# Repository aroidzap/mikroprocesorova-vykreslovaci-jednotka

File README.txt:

Copyright (c) 2015 Tomá Pazdiora

Documents, images, code, schematics and boards.

Documents, images, all schematic (.sch) and board (.brd) files are licenced under CC-BY 4.0 (http://creativecommons.org/licenses/by/4.0/legalcode)
All source code is licensed under MIT license. See the file "LICENSE.txt" for full license text.

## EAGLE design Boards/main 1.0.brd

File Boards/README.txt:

You can view and export boards using CadSoft's EAGLE Light Edition. (available from: http://www.cadsoftusa.com/download-eagle/freeware/)

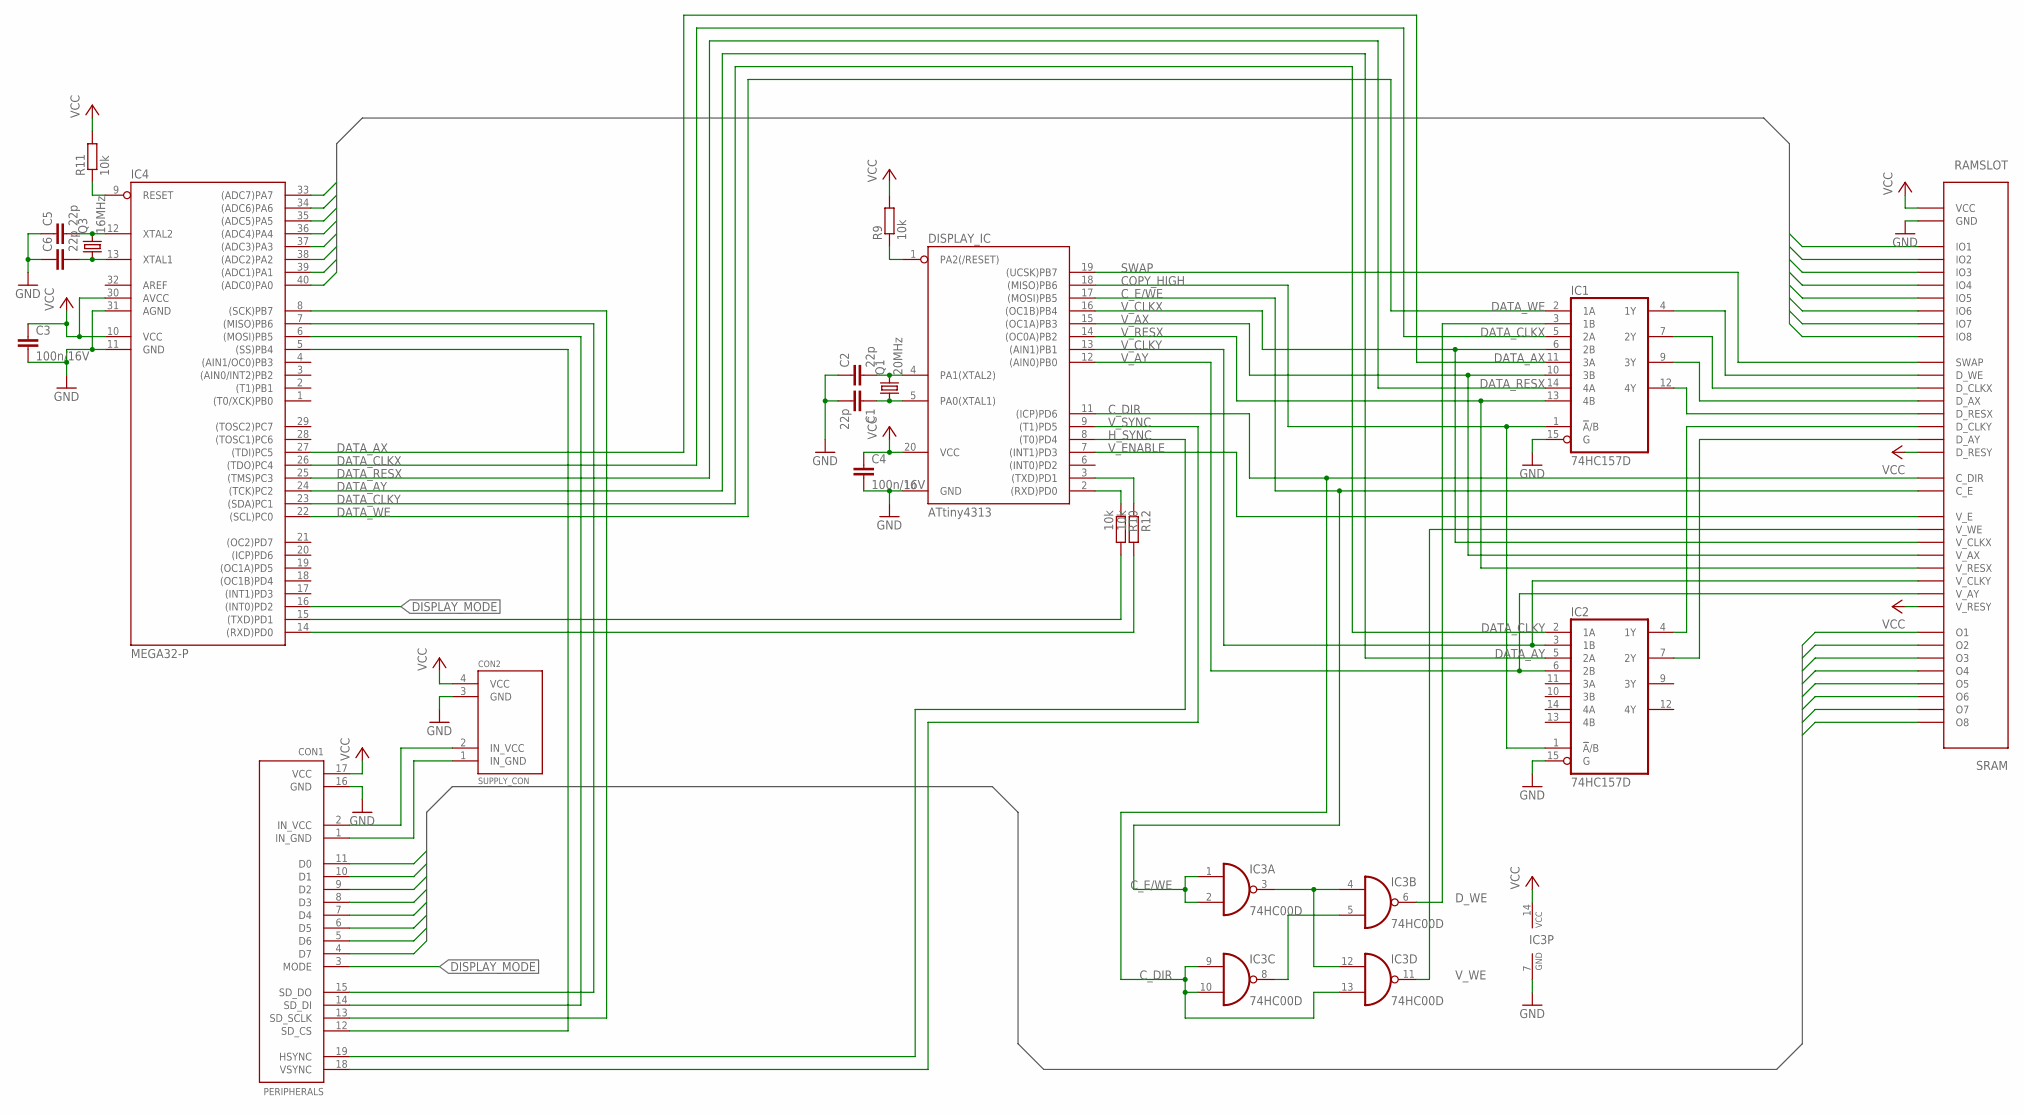
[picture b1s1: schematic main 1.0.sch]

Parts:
C1, C2, C5, C6: 22p; C0603
C3, C4: 100n/16V; C0603
CON1: PERIPHERALS; PERIPHERALS_CON
CON2: SUPPLY_CON
DISPLAY_IC: ATtiny4313; DIL20
IC1, IC2: 74HC157D; SO16
IC3: 74HC00D; SO14
IC4: MEGA32-P; DIL40
Q1: 20MHz; HC49
Q3: 16MHz; HC49
R9, R10, R11, R12: 10k; R0603
RAMSLOT: SRAM; SLOT

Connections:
AREF: IC4.32 (AREF)
COPY_HIGH: DISPLAY_IC.18 ((MISO)PB6), IC1.1 (!A!/B), IC2.1 (!A!/B)
C_DIR: DISPLAY_IC.11 ((ICP)PD6), IC3.9 (I0), IC3.10 (I1), IC3.13 (I1), RAMSLOT.C_DIR, RAMSLOT.C_DIRB (C_DIR)
C_E/WE: DISPLAY_IC.17 ((MOSI)PB5), IC3.1 (I0), IC3.2 (I1), RAMSLOT.C_E, RAMSLOT.C_EB (C_E)
DATA0: IC4.40 ((ADC0)PA0), RAMSLOT.IO1, RAMSLOT.IO1B (IO1)
DATA1: IC4.39 ((ADC1)PA1), RAMSLOT.IO2, RAMSLOT.IO2B (IO2)
DATA2: IC4.38 ((ADC2)PA2), RAMSLOT.IO3, RAMSLOT.IO3B (IO3)
DATA3: IC4.37 ((ADC3)PA3), RAMSLOT.IO4, RAMSLOT.IO4B (IO4)
DATA4: IC4.36 ((ADC4)PA4), RAMSLOT.IO5, RAMSLOT.IO5B (IO5)
DATA5: IC4.35 ((ADC5)PA5), RAMSLOT.IO6, RAMSLOT.IO6B (IO6)
DATA6: IC4.34 ((ADC6)PA6), RAMSLOT.IO7, RAMSLOT.IO7B (IO7)
DATA7: IC4.33 ((ADC7)PA7), RAMSLOT.IO8, RAMSLOT.IO8B (IO8)
DATA_AX: IC1.11 (3A), IC4.27 ((TDI)PC5)
DATA_AY: IC2.5 (2A), IC4.24 ((TCK)PC2)
DATA_CLKX: IC1.5 (2A), IC4.26 ((TDO)PC4)
DATA_CLKY: IC2.2 (1A), IC4.23 ((SDA)PC1)
DATA_RESX: IC1.14 (4A), IC4.25 ((TMS)PC3)
DATA_WE: IC1.2 (1A), IC4.22 ((SCL)PC0)
DISPLAY_MODE: CON1.3 (MODE), IC4.16 ((INT0)PD2)
D_WE: IC1.3 (1B), IC3.6 (O)
GND: C1.2, C2.1, C3.2, C4.2, C5.1, C6.1, CON1.16 (GND), CON2.3 (GND), DISPLAY_IC.10 (GND), IC1.8 (GND), IC1.15 (G), IC2.8 (GND), IC2.15 (G), IC3.7 (GND), IC4.11 (GND), IC4.31 (AGND), RAMSLOT.GND, RAMSLOT.GNDB (GND)
H_SYNC: CON1.19 (HSYNC), DISPLAY_IC.8 ((T0)PD4)
IN_GND: CON1.1 (IN_GND), CON2.1 (IN_GND)
MAIN_RX: IC4.14 ((RXD)PD0), R12.2
MAIN_TX: IC4.15 ((TXD)PD1), R10.2
unnamed: IC4.9 (RESET), R11.1
unnamed: IC3.3 (O), IC3.4 (I0), IC3.12 (I0)
unnamed: IC3.5 (I1), IC3.8 (O)
unnamed: CON1.2 (IN_VCC), CON2.2 (IN_VCC)
unnamed: DISPLAY_IC.1 (PA2(/RESET)), R9.1
unnamed: DISPLAY_IC.3 ((TXD)PD1), R12.1
unnamed: C5.2, IC4.12 (XTAL2), Q3.2
unnamed: C6.2, IC4.13 (XTAL1), Q3.1
unnamed: DISPLAY_IC.2 ((RXD)PD0), R10.1
unnamed: C1.1, DISPLAY_IC.5 (PA0(XTAL1)), Q1.1
unnamed: C2.2, DISPLAY_IC.4 (PA1(XTAL2)), Q1.2
unnamed: IC1.4 (1Y), RAMSLOT.D_WE, RAMSLOT.D_WEB (D_WE)
unnamed: IC1.7 (2Y), RAMSLOT.D_CLKX, RAMSLOT.D_CLKXB (D_CLKX)
unnamed: IC1.9 (3Y), RAMSLOT.D_AX, RAMSLOT.D_AXB (D_AX)
unnamed: IC1.12 (4Y), RAMSLOT.D_RESX, RAMSLOT.D_RESXB (D_RESX)
unnamed: IC2.4 (1Y), RAMSLOT.D_CLKY, RAMSLOT.D_CLKYB (D_CLKY)
unnamed: IC2.7 (2Y), RAMSLOT.D_AY, RAMSLOT.D_AYB (D_AY)
O0: CON1.11 (D0), RAMSLOT.O1, RAMSLOT.O1B (O1)
O1: CON1.10 (D1), RAMSLOT.O2, RAMSLOT.O2B (O2)
O2: CON1.9 (D2), RAMSLOT.O3, RAMSLOT.O3B (O3)
O3: CON1.8 (D3), RAMSLOT.O4, RAMSLOT.O4B (O4)
O4: CON1.7 (D4), RAMSLOT.O5, RAMSLOT.O5B (O5)
O5: CON1.6 (D5), RAMSLOT.O6, RAMSLOT.O6B (O6)
O6: CON1.5 (D6), RAMSLOT.O7, RAMSLOT.O7B (O7)
O7: CON1.4 (D7), RAMSLOT.O8, RAMSLOT.O8B (O8)
SD_CS: CON1.12 (SD_CS), IC4.5 ((SS)PB4)
SD_DI: CON1.14 (SD_DI), IC4.6 ((MOSI)PB5)
SD_DO: CON1.15 (SD_DO), IC4.7 ((MISO)PB6)
SD_SCLK: CON1.13 (SD_SCLK), IC4.8 ((SCK)PB7)
SWAP: DISPLAY_IC.19 ((UCSK)PB7), RAMSLOT.SWAP, RAMSLOT.SWAPB (SWAP)
VCC: C3.1, C4.1, CON1.17 (VCC), CON2.4 (VCC), DISPLAY_IC.20 (VCC), IC1.16 (VCC), IC2.16 (VCC), IC3.14 (VCC), IC4.10 (VCC), IC4.30 (AVCC), R9.2, R11.2, RAMSLOT.D_RESY, RAMSLOT.D_RESYB (D_RESY), RAMSLOT.VCC, RAMSLOT.VCCB (VCC), RAMSLOT.V_RESY, RAMSLOT.V_RESYB (V_RESY)
V_AX: DISPLAY_IC.15 ((OC1A)PB3), IC1.10 (3B), RAMSLOT.V_AX, RAMSLOT.V_AXB (V_AX)
V_AY: DISPLAY_IC.12 ((AIN0)PB0), IC2.6 (2B), RAMSLOT.V_AY, RAMSLOT.V_AYB (V_AY)
V_CLKX: DISPLAY_IC.16 ((OC1B)PB4), IC1.6 (2B), RAMSLOT.V_CLKX, RAMSLOT.V_CLKXB (V_CLKX)
V_CLKY: DISPLAY_IC.13 ((AIN1)PB1), IC2.3 (1B), RAMSLOT.V_CLKY, RAMSLOT.V_CLKYB (V_CLKY)
V_ENABLE: DISPLAY_IC.7 ((INT1)PD3), RAMSLOT.V_E, RAMSLOT.V_EB (V_E)
V_RESX: DISPLAY_IC.14 ((OC0A)PB2), IC1.13 (4B), RAMSLOT.V_RESX, RAMSLOT.V_RESXB (V_RESX)
V_SYNC: CON1.18 (VSYNC), DISPLAY_IC.9 ((T1)PD5)
V_WE: IC3.11 (O), RAMSLOT.V_WE, RAMSLOT.V_WEB (V_WE)

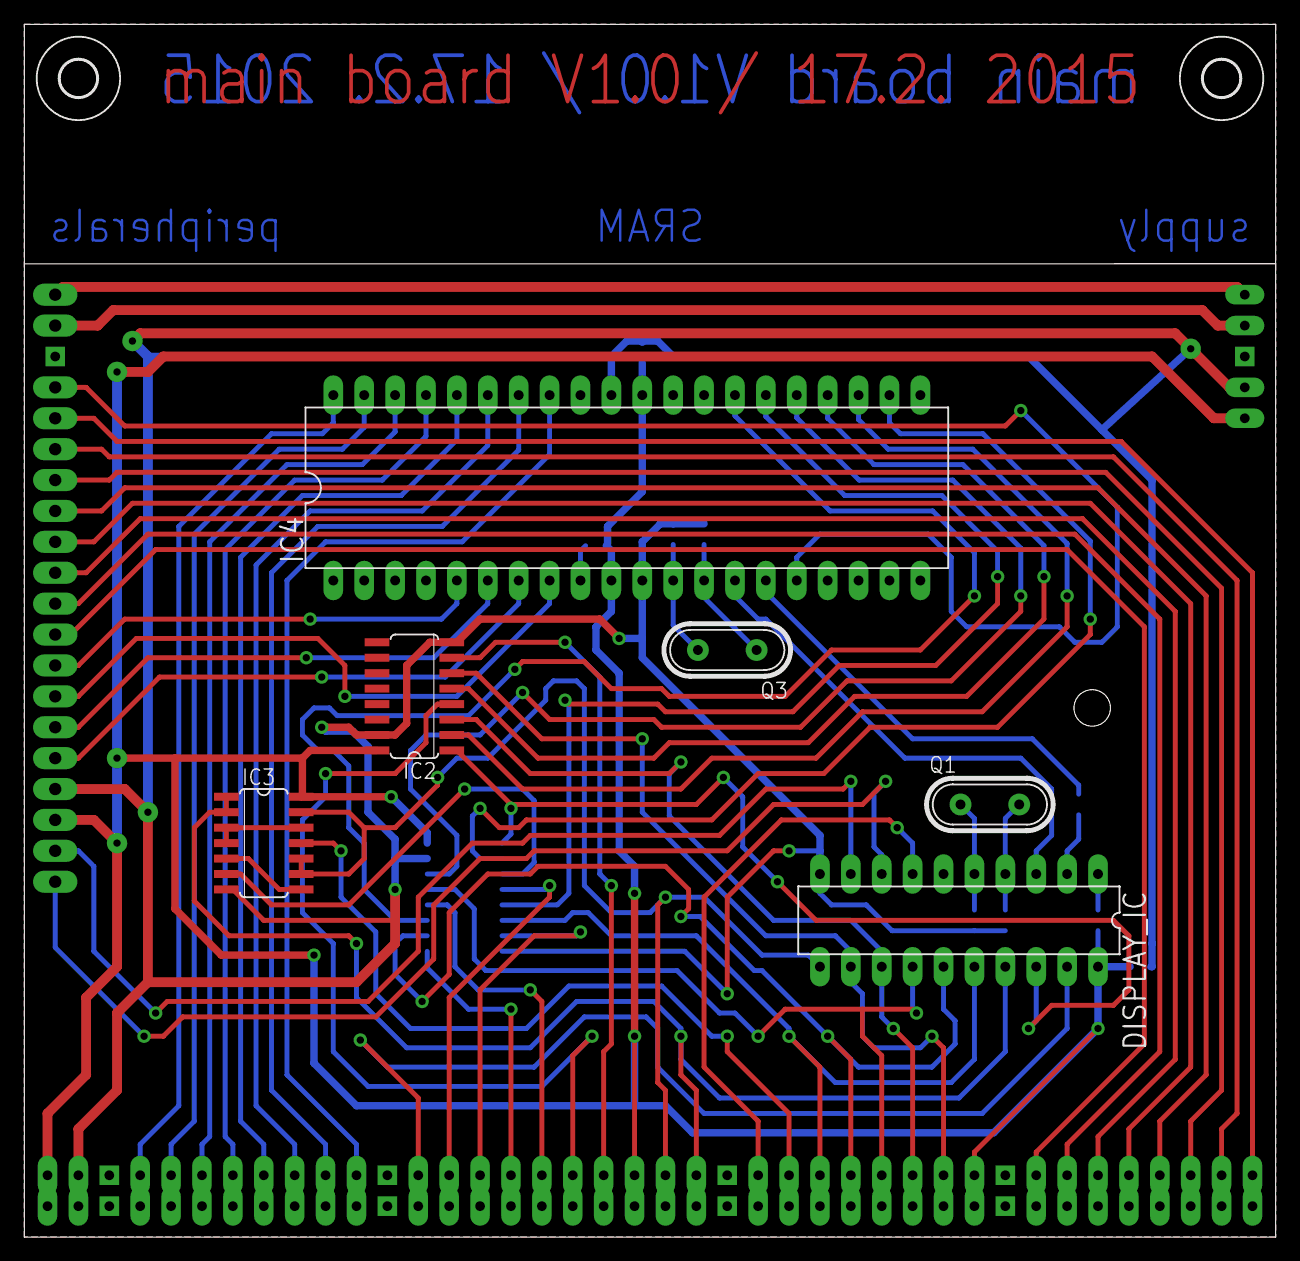
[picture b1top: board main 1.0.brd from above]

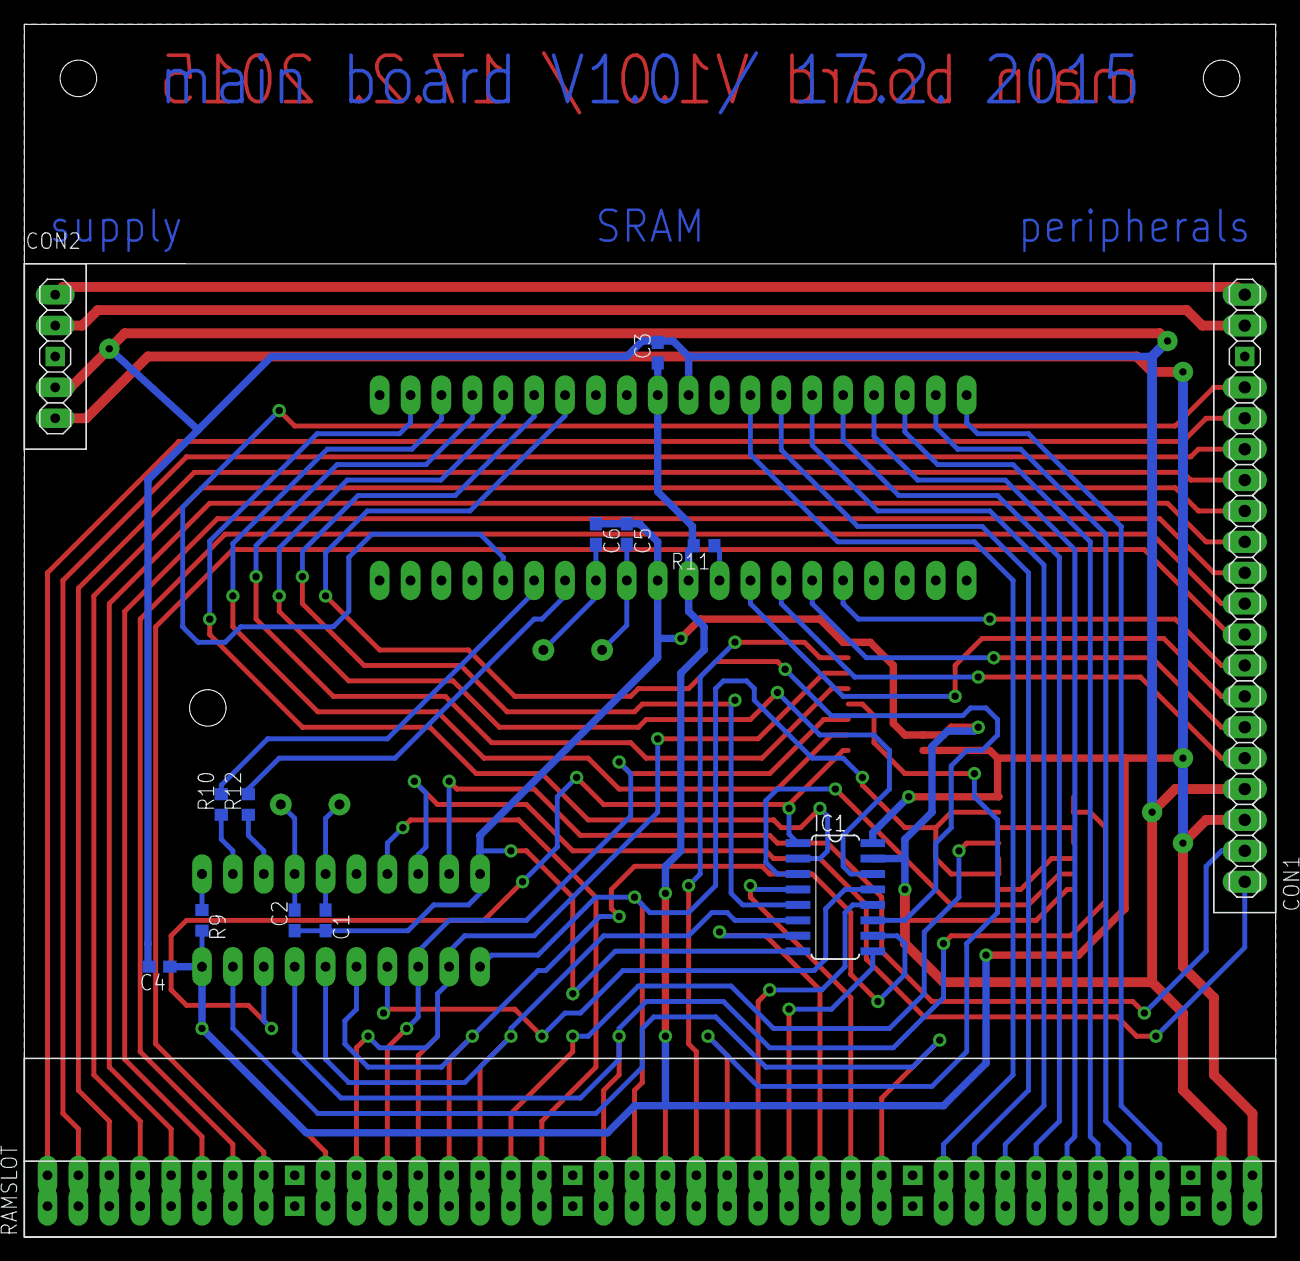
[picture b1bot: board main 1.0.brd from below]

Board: 2 copper layers, 102.9 x 99.7 mm, 22 parts (14 on the bottom side), 63 nets.

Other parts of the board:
U$1, U$2: 3,0

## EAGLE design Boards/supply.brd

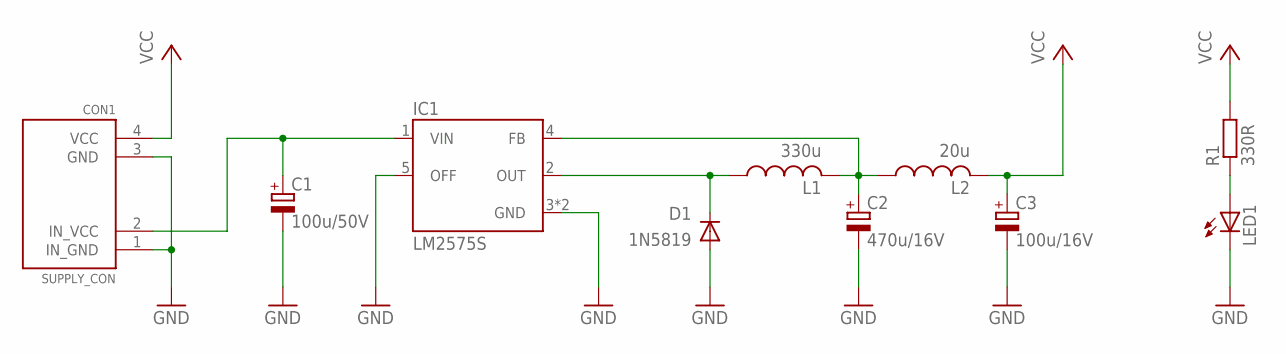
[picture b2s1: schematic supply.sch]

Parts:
C1: 100u/50V; E3,5-8
C2: 470u/16V; E5-10,5
C3: 100u/16V; E2,5-6
CON1: SUPPLY_CON
D1: 1N5819; DO41-10
IC1: LM2575S; TO263-5
L1: 330u; COIL
L2: 20u; COIL
LED1: LEDSML1206; SML1206
R1: 330R; R0603

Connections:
GND: C1.-, C2.-, C3.-, CON1.1 (IN_GND), CON1.3 (GND), D1.A, IC1.3 (GND), IC1.5 (OFF), IC1.6 (GND), LED1.C
IN_VCC: C1.+, CON1.2 (IN_VCC), IC1.1 (VIN)
unnamed: C2.+, IC1.4 (FB), L1.P$2, L2.P$1
unnamed: LED1.A, R1.1
unnamed: D1.C, IC1.2 (OUT), L1.P$1
VCC: C3.+, CON1.4 (VCC), L2.P$2, R1.2

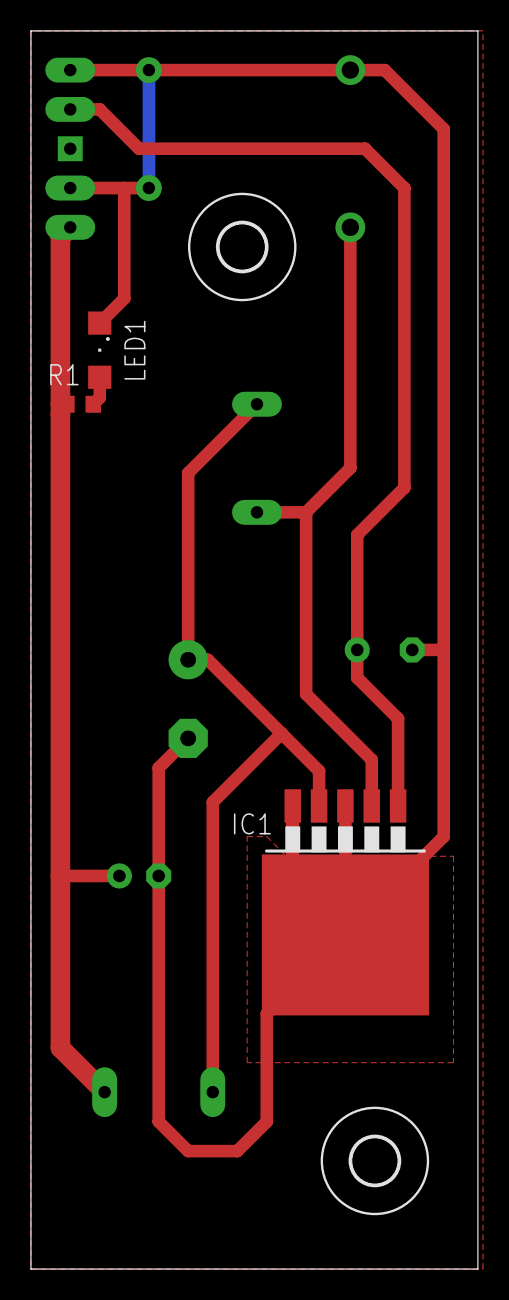
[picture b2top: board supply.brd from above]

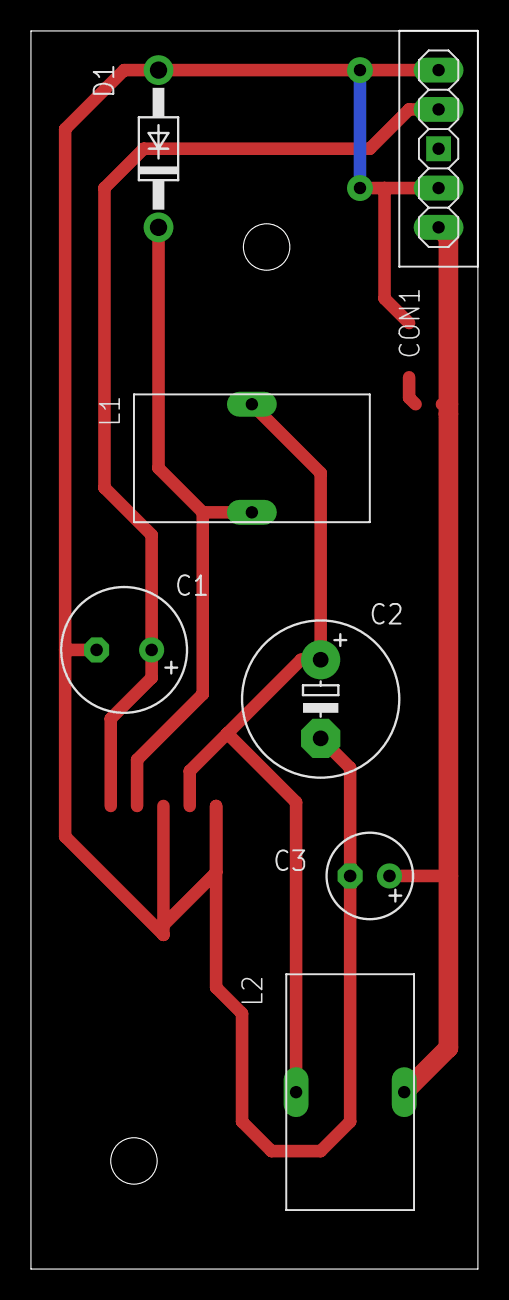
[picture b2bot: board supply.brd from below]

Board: 2 copper layers, 28.9 x 80.0 mm, 12 parts (7 on the bottom side), 6 nets.

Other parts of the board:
U$1, U$2: 3,0

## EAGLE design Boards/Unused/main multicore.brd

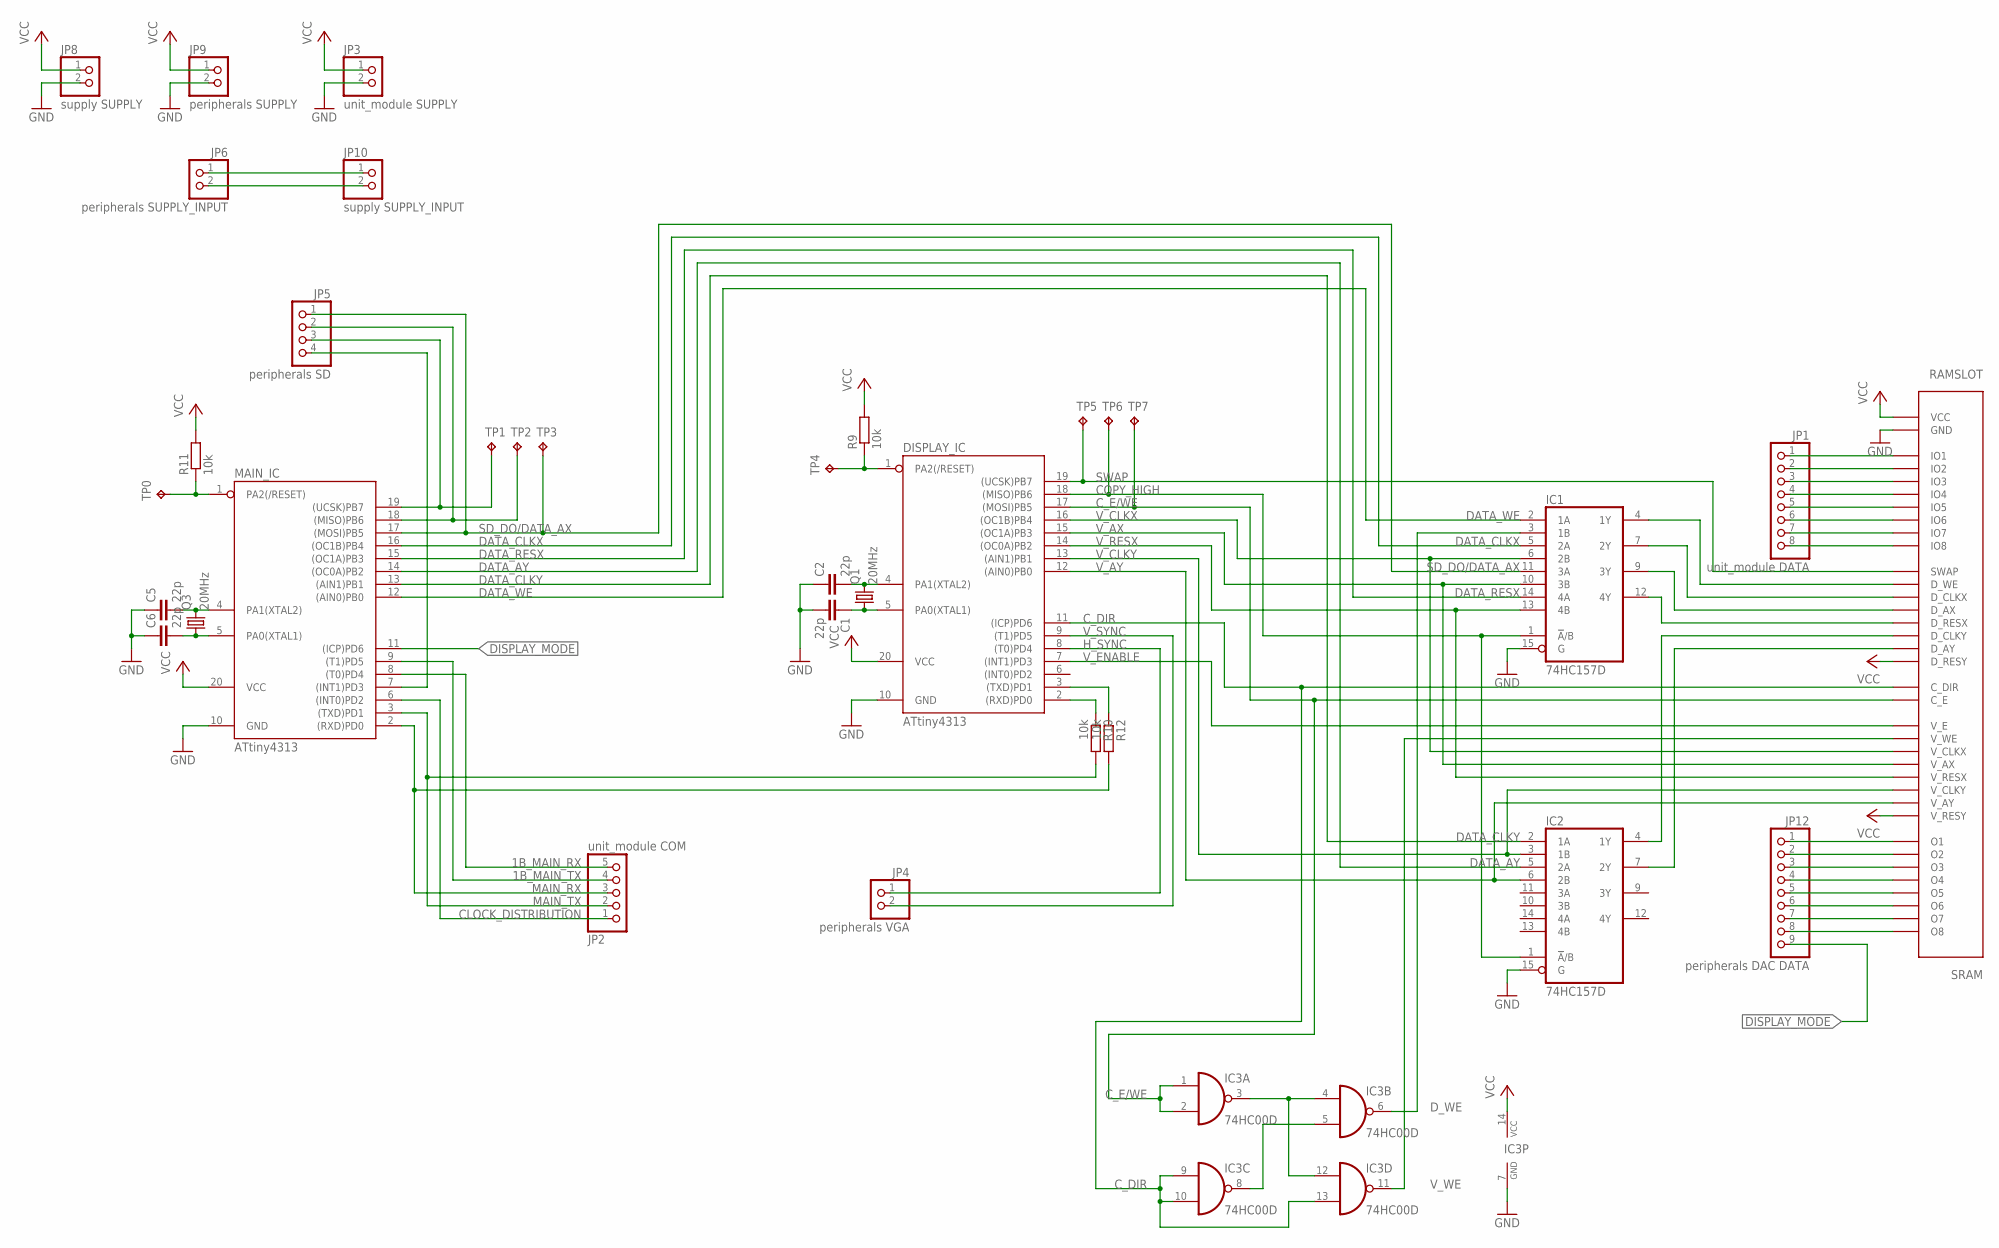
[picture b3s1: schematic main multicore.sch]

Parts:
C1, C2, C5, C6: 22p; C0402
DISPLAY_IC: ATtiny4313; SO20L$
IC1, IC2: 74HC157D; SO16
IC3: 74HC00D; SO14
JP1: unit_module DATA; 1X08
JP2: unit_module COM; 1X05
JP3: unit_module SUPPLY; 1X02
JP4: peripherals VGA; 1X02
JP5: peripherals SD; 1X04
JP6: peripherals SUPPLY_INPUT; 1X02
JP8: supply SUPPLY; 1X02
JP9: peripherals SUPPLY; 1X02
JP10: supply SUPPLY_INPUT; 1X02
JP12: peripherals DAC DATA; 1X09
MAIN_IC: ATtiny4313; SO20L$
Q1, Q3: 20MHz; MC-405
R9, R10, R11, R12: 10k; R0603
RAMSLOT: SRAM; SLOT
TP0, TP1, TP2, TP3, TP4, TP5, TP6, TP7: TPB1,27; B1,27

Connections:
1B_MAIN_RX: JP2.5, MAIN_IC.8 ((T0)PD4)
1B_MAIN_TX: JP2.4, MAIN_IC.9 ((T1)PD5)
CLOCK_DISTRIBUTION: JP2.1, MAIN_IC.6 ((INT0)PD2)
COPY_HIGH: DISPLAY_IC.18 ((MISO)PB6), IC1.1 (!A!/B), IC2.1 (!A!/B), TP6.TP
C_DIR: DISPLAY_IC.11 ((ICP)PD6), IC3.9 (I0), IC3.10 (I1), IC3.13 (I1), RAMSLOT.C_DIR
C_E/WE: DISPLAY_IC.17 ((MOSI)PB5), IC3.1 (I0), IC3.2 (I1), RAMSLOT.C_E, TP7.TP
DATA_AY: IC2.5 (2A), MAIN_IC.14 ((OC0A)PB2)
DATA_CLKX: IC1.5 (2A), MAIN_IC.16 ((OC1B)PB4)
DATA_CLKY: IC2.2 (1A), MAIN_IC.13 ((AIN1)PB1)
DATA_RESX: IC1.14 (4A), MAIN_IC.15 ((OC1A)PB3)
DATA_WE: IC1.2 (1A), MAIN_IC.12 ((AIN0)PB0)
DISPLAY_MODE: JP12.9, MAIN_IC.11 ((ICP)PD6)
D_WE: IC1.3 (1B), IC3.6 (O)
GND: C1.2, C2.1, C5.1, C6.1, DISPLAY_IC.10 (GND), IC1.8 (GND), IC1.15 (G), IC2.8 (GND), IC2.15 (G), IC3.7 (GND), JP3.2, JP8.2, JP9.2, MAIN_IC.10 (GND), RAMSLOT.GND
H_SYNC: DISPLAY_IC.8 ((T0)PD4), JP4.1
IN_GND: JP6.2, JP10.2
IN_VCC: JP6.1, JP10.1
MAIN_RX: JP2.3, MAIN_IC.2 ((RXD)PD0), R12.2
MAIN_TX: JP2.2, MAIN_IC.3 ((TXD)PD1), R10.2
unnamed: IC3.3 (O), IC3.4 (I0), IC3.12 (I0)
unnamed: IC3.5 (I1), IC3.8 (O)
unnamed: JP1.1, RAMSLOT.IO1
unnamed: DISPLAY_IC.1 (PA2(/RESET)), R9.1, TP4.TP
unnamed: JP1.2, RAMSLOT.IO2
unnamed: JP1.3, RAMSLOT.IO3
unnamed: DISPLAY_IC.3 ((TXD)PD1), R12.1
unnamed: C5.2, MAIN_IC.4 (PA1(XTAL2)), Q3.2
unnamed: C6.2, MAIN_IC.5 (PA0(XTAL1)), Q3.1
unnamed: MAIN_IC.1 (PA2(/RESET)), R11.1, TP0.TP
unnamed: JP1.4, RAMSLOT.IO4
unnamed: JP1.5, RAMSLOT.IO5
unnamed: JP1.6, RAMSLOT.IO6
unnamed: JP1.7, RAMSLOT.IO7
unnamed: JP1.8, RAMSLOT.IO8
unnamed: DISPLAY_IC.2 ((RXD)PD0), R10.1
unnamed: C1.1, DISPLAY_IC.5 (PA0(XTAL1)), Q1.1
unnamed: C2.2, DISPLAY_IC.4 (PA1(XTAL2)), Q1.2
unnamed: JP12.1, RAMSLOT.O1
unnamed: JP12.2, RAMSLOT.O2
unnamed: JP12.3, RAMSLOT.O3
unnamed: JP12.4, RAMSLOT.O4
unnamed: JP12.5, RAMSLOT.O5
unnamed: JP12.6, RAMSLOT.O6
unnamed: JP12.7, RAMSLOT.O7
unnamed: JP12.8, RAMSLOT.O8
unnamed: IC1.4 (1Y), RAMSLOT.D_WE
unnamed: IC1.7 (2Y), RAMSLOT.D_CLKX
unnamed: IC1.9 (3Y), RAMSLOT.D_AX
unnamed: IC1.12 (4Y), RAMSLOT.D_RESX
unnamed: IC2.4 (1Y), RAMSLOT.D_CLKY
unnamed: IC2.7 (2Y), RAMSLOT.D_AY
SD_CS: JP5.4, MAIN_IC.7 ((INT1)PD3)
SD_DI: JP5.2, MAIN_IC.18 ((MISO)PB6), TP2.TP
SD_DO/DATA_AX: IC1.11 (3A), JP5.1, MAIN_IC.17 ((MOSI)PB5), TP3.TP
SD_SCLK: JP5.3, MAIN_IC.19 ((UCSK)PB7), TP1.TP
SWAP: DISPLAY_IC.19 ((UCSK)PB7), RAMSLOT.SWAP, TP5.TP
VCC: DISPLAY_IC.20 (VCC), IC1.16 (VCC), IC2.16 (VCC), IC3.14 (VCC), JP3.1, JP8.1, JP9.1, MAIN_IC.20 (VCC), R9.2, R11.2, RAMSLOT.D_RESY, RAMSLOT.VCC, RAMSLOT.V_RESY
V_AX: DISPLAY_IC.15 ((OC1A)PB3), IC1.10 (3B), RAMSLOT.V_AX
V_AY: DISPLAY_IC.12 ((AIN0)PB0), IC2.6 (2B), RAMSLOT.V_AY
V_CLKX: DISPLAY_IC.16 ((OC1B)PB4), IC1.6 (2B), RAMSLOT.V_CLKX
V_CLKY: DISPLAY_IC.13 ((AIN1)PB1), IC2.3 (1B), RAMSLOT.V_CLKY
V_ENABLE: DISPLAY_IC.7 ((INT1)PD3), RAMSLOT.V_E
V_RESX: DISPLAY_IC.14 ((OC0A)PB2), IC1.13 (4B), RAMSLOT.V_RESX
V_SYNC: DISPLAY_IC.9 ((T1)PD5), JP4.2
V_WE: IC3.11 (O), RAMSLOT.V_WE

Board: 2 copper layers, 34 parts (0 on the bottom side), 65 nets, no tracks yet.

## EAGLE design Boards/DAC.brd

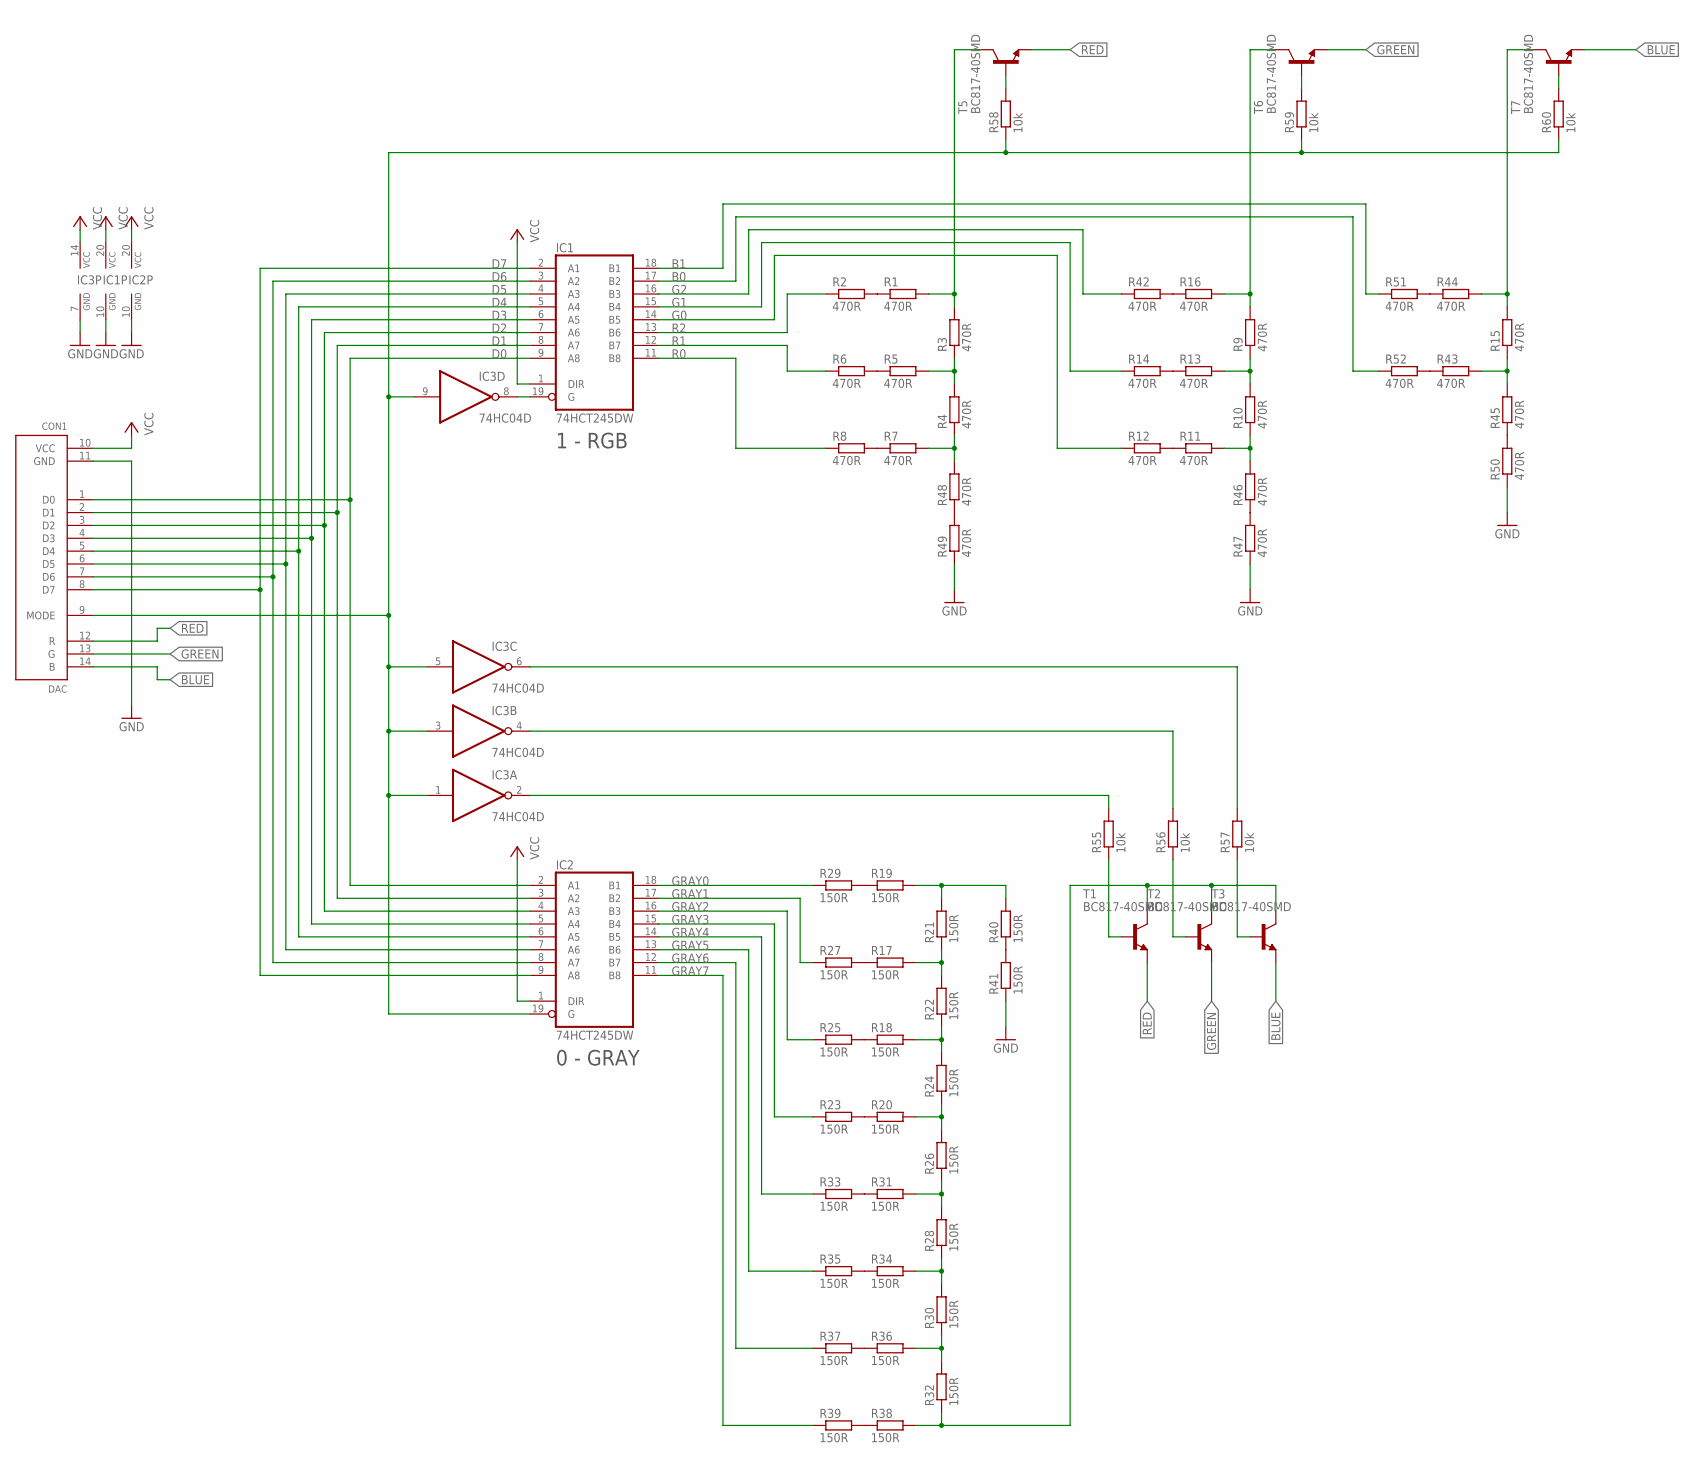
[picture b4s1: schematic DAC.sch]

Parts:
CON1: DAC; DAC_CON
IC1, IC2: 74HCT245DW; SO20W
IC3: 74HC04D; SO14
R1, R2, R3, R4, R5, R6, R7, R8, R9, R10, R11, R12, R13, R14, R15, R16, R42, R43, R44, R45, R46, R47, R48, R49, R50, R51, R52: 470R; R0603
R17, R18, R19, R20, R21, R22, R23, R24, R25, R26, R27, R28, R29, R30, R31, R32, R33, R34, R35, R36, R37, R38, R39, R40, R41: 150R; R0603
R55, R56, R57, R58, R59, R60: 10k; R0603
T1, T2, T3, T5, T6, T7: BC817-40SMD; SOT23-BEC

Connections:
B0: IC1.17 (B2), R52.1
B1: IC1.18 (B1), R51.1
BLUE: CON1.14 (B), T3.E, T7.E
D0: CON1.1 (D0), IC1.9 (A8), IC2.2 (A1)
D1: CON1.2 (D1), IC1.8 (A7), IC2.3 (A2)
D2: CON1.3 (D2), IC1.7 (A6), IC2.4 (A3)
D3: CON1.4 (D3), IC1.6 (A5), IC2.5 (A4)
D4: CON1.5 (D4), IC1.5 (A4), IC2.6 (A5)
D5: CON1.6 (D5), IC1.4 (A3), IC2.7 (A6)
D6: CON1.7 (D6), IC1.3 (A2), IC2.8 (A7)
D7: CON1.8 (D7), IC1.2 (A1), IC2.9 (A8)
DAC_BLUE: R15.2, R44.2, T7.C
DAC_GRAY: R32.1, R38.2, T1.C, T2.C, T3.C
DAC_GREEN: R9.2, R16.2, T6.C
DAC_RED: R1.2, R3.2, T5.C
G0: IC1.14 (B5), R12.1
G1: IC1.15 (B4), R14.1
G2: IC1.16 (B3), R42.1
GND: CON1.11 (GND), IC1.10 (GND), IC2.10 (GND), IC3.7 (GND), R41.1, R47.1, R49.1, R50.1
GRAY0: IC2.18 (B1), R29.1
GRAY1: IC2.17 (B2), R27.1
GRAY2: IC2.16 (B3), R25.1
GRAY3: IC2.15 (B4), R23.1
GRAY4: IC2.14 (B5), R33.1
GRAY5: IC2.13 (B6), R35.1
GRAY6: IC2.12 (B7), R37.1
GRAY7: IC2.11 (B8), R39.1
GREEN: CON1.13 (G), T2.E, T6.E
unnamed: R9.1, R10.2, R13.2
unnamed: R3.1, R4.2, R5.2
unnamed: R4.1, R7.2, R48.2
unnamed: R10.1, R11.2, R46.2
unnamed: R15.1, R43.2, R45.2
unnamed: R20.1, R23.2
unnamed: R17.2, R21.1, R22.2
unnamed: R18.2, R22.1, R24.2
unnamed: R20.2, R24.1, R26.2
unnamed: R26.1, R28.2, R31.2
unnamed: R28.1, R30.2, R34.2
unnamed: R30.1, R32.2, R36.2
unnamed: R18.1, R25.2
unnamed: R17.1, R27.2
unnamed: R19.1, R29.2
unnamed: R31.1, R33.2
unnamed: R34.1, R35.2
unnamed: R36.1, R37.2
unnamed: R38.1, R39.2
unnamed: R40.1, R41.2
unnamed: R1.1, R2.2
unnamed: R5.1, R6.2
unnamed: R7.1, R8.2
unnamed: R11.1, R12.2
unnamed: R13.1, R14.2
unnamed: R16.1, R42.2
unnamed: R46.1, R47.2
unnamed: R48.1, R49.2
unnamed: R45.1, R50.2
unnamed: R44.1, R51.2
unnamed: R43.1, R52.2
unnamed: R19.2, R21.2, R40.2
unnamed: IC1.19 (G), IC3.8 (O)
unnamed: IC3.2 (O), R55.2
unnamed: R58.2, T5.B
unnamed: IC3.4 (O), R56.2
unnamed: R59.2, T6.B
unnamed: R55.1, T1.B
unnamed: R56.1, T2.B
unnamed: R57.1, T3.B
unnamed: R60.2, T7.B
unnamed: CON1.9 (MODE), IC2.19 (G), IC3.1 (I), IC3.3 (I), IC3.5 (I), IC3.9 (I), R58.1, R59.1, R60.1
unnamed: IC3.6 (O), R57.2
R0: IC1.11 (B8), R8.1
R1: IC1.12 (B7), R6.1
R2: IC1.13 (B6), R2.1
RED: CON1.12 (R), T1.E, T5.E
VCC: CON1.10 (VCC), IC1.1 (DIR), IC1.20 (VCC), IC2.1 (DIR), IC2.20 (VCC), IC3.14 (VCC)

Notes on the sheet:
0 - GRAY
1 - RGB

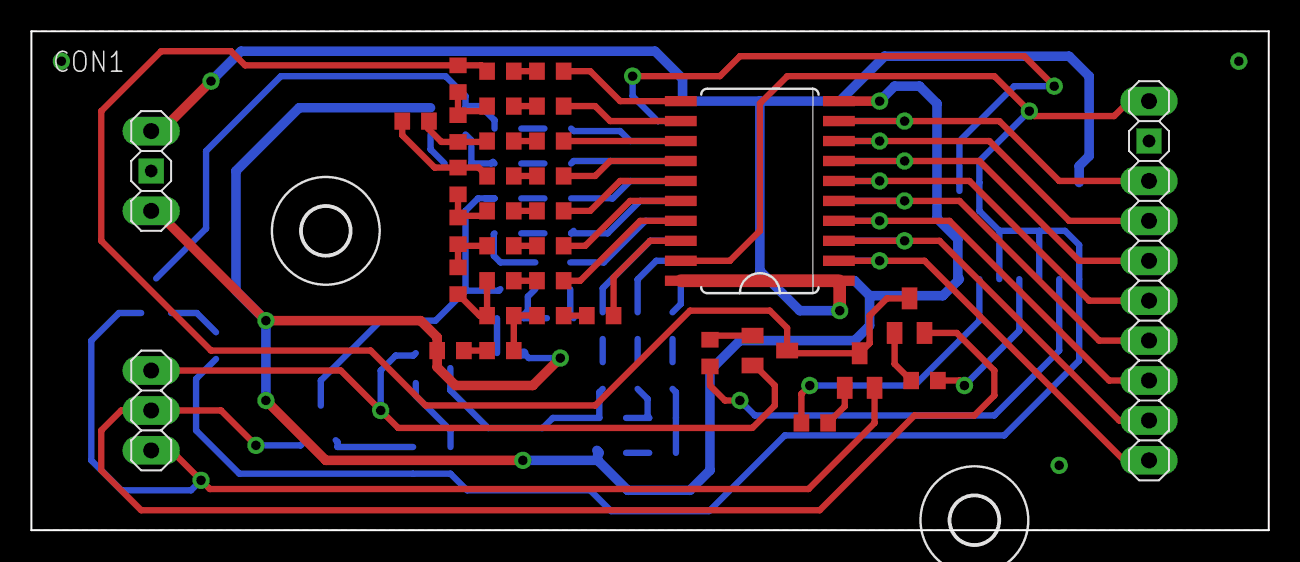
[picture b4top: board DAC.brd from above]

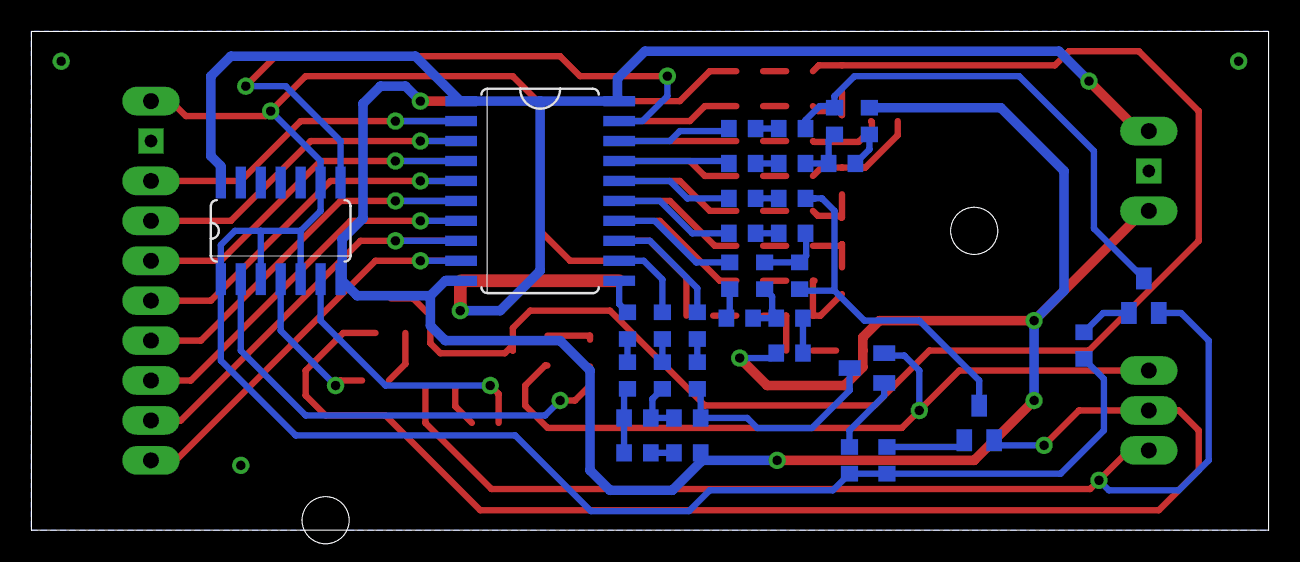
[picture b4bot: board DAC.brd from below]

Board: 2 copper layers, 78.7 x 31.7 mm, 70 parts (35 on the bottom side), 76 nets.

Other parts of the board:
U$1, U$2: 3,0

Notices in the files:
Display microprocessor/VGA_driver_settings.h:
Copyright (c) 2015 Tomáš Pazdiora
